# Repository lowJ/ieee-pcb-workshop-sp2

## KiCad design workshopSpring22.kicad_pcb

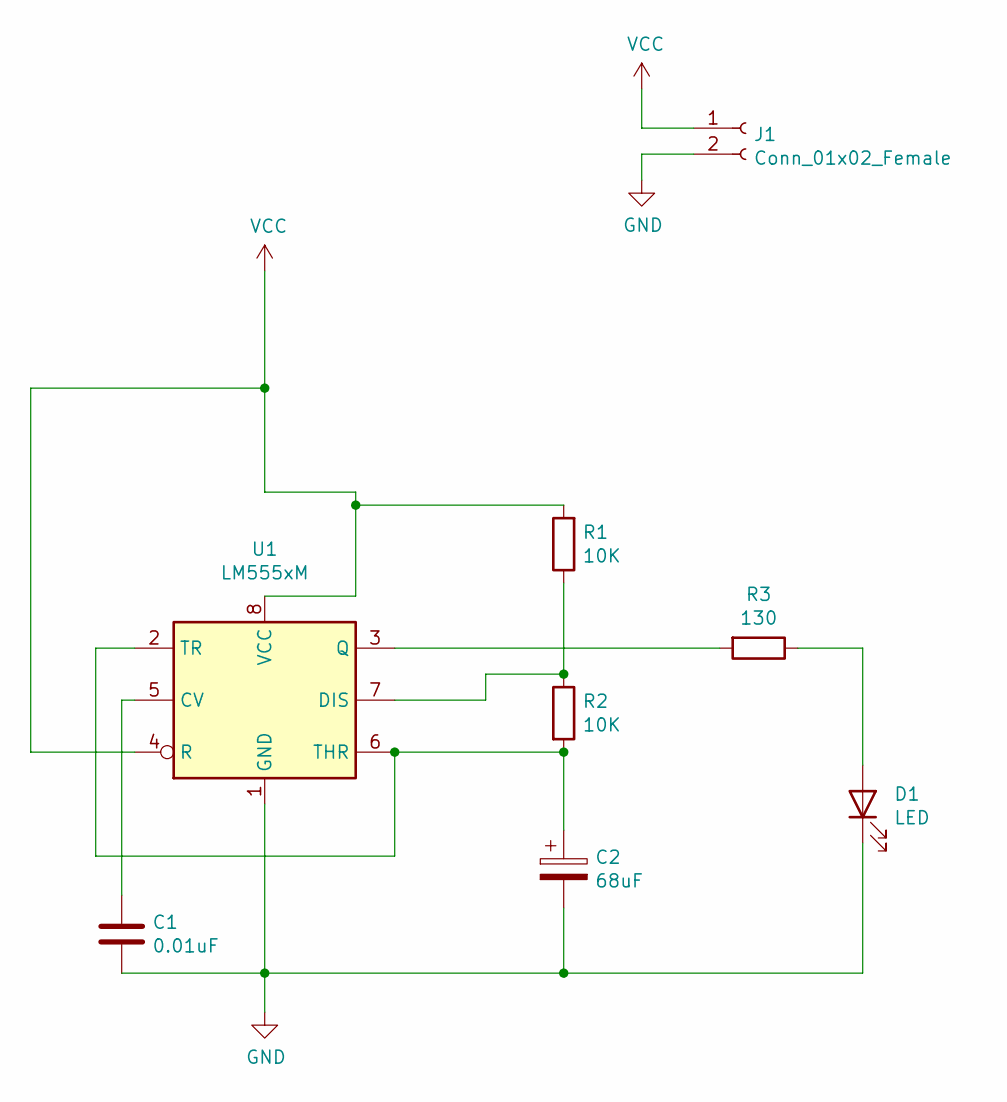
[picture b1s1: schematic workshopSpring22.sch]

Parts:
C1: 0.01uF; C_Radial_D4.0mm_H5.0mm_P1.50mm
C2: 68uF; C_Radial_D4.0mm_H5.0mm_P1.50mm
D1: LED; LED_D4.0mm
J1: Conn_01x02_Female; PinHeader_1x02_P2.54mm_Vertical
R1, R2: 10K; R_1206_3216Metric_Pad1.30x1.75mm_HandSolder
R3: 130; R_Axial_DIN0207_L6.3mm_D2.5mm_P10.16mm_Horizontal
U1: LM555xM; SOIC-8_3.9x4.9mm_P1.27mm

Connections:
GND: C1.2, C2.2, D1.1 (K), J1.2, U1.1 (GND)
unnamed: C1.1, U1.5 (CV)
unnamed: C2.1, R2.2, U1.2 (TR), U1.6 (THR)
unnamed: D1.2 (A), R3.1
unnamed: R1.1, R2.1, U1.7 (DIS)
unnamed: R3.2, U1.3 (Q)
VCC: J1.1, R1.2, U1.4 (R), U1.8 (VCC)

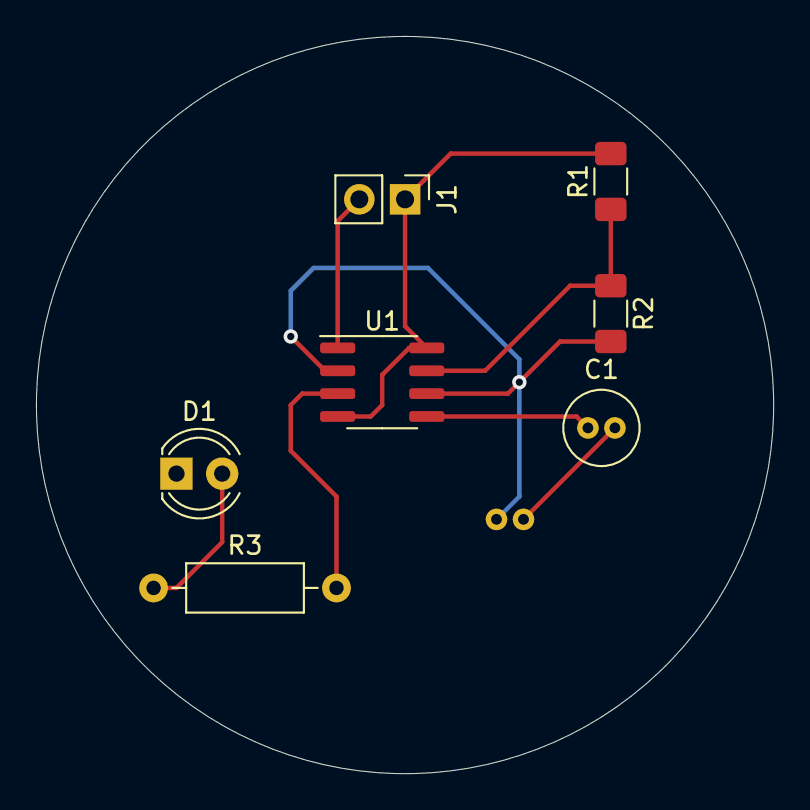
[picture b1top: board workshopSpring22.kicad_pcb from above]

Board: 2 copper layers, 41.0 x 41.0 mm, 8 parts (1 on the bottom side), 7 nets.

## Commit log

2022-03-31 first
